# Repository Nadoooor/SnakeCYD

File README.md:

# SnakeCYD
--------------

--------------------------------

## Description:
SnakeCYD is a custom CYD, all in an PCB with snake slickscreen and with ESP32-s3 instead of a regular ESP32 chip.

## Why iam making this:
I was planning to get a CYD, but I got to know that it has a regular ESP32 on it instead of the S3, so i decided to make my own and add my snake slikscreen and also added bigger connectors for the wiring protocols and also some free pins.

## Featrues:

* Big JST connectors
* Free GPIO with PinSockets
* USB Type C
* Onboard Neopixel
* ESP32-S3 chip inside.

## Photos:

### PCB:

### 3D PCB:

### Schematic:
#### First Page:
--------------------

----------------------------
#### Second Page:

## Pinout:
| ESP32-S3 Pin Label | Signal / Net Name |
| :--- | :--- |
| **IO1** | `TFT_BL` |
| **IO4** | `TFT_DC` |
| **IO5** | `I2C_SDA` |
| **IO6** | `I2C_SCL` |
| **IO7** | `SPI_MOIS` |
| **IO8** | `SPI_CLK` |
| **IO9** | `SPI_MISO` |
| **IO10** | `ANY_CS` |
| **IO11** | `SPI2_MOIS` |
| **IO12** | `SPI2_CLK` |
| **IO13** | `SPI2_MISO` |
| **IO14** | `TFT_CS` |
| **IO15** | `T_CS` |
| **IO16** | `SD_CS` |
| **IO17** | `TX` |
| **IO18** | `RX` |
| **IO21** | `T_IRQ` |
| **TXD0** | `0TX` |
| **RXD0** | `0RX` |

## How to use:
1. Connect the SnakeCYD to you PC/Laptop.
2. Download the firmware source code you want to use.
3. Edit the pinout using the table above.
4. Build the firmware and flash it.
5. Enjoy.

## How to build:
1. Print the board.
2. Assemble all the components.
3. Enjoy.

# Made with ❤️, By Nadoooor

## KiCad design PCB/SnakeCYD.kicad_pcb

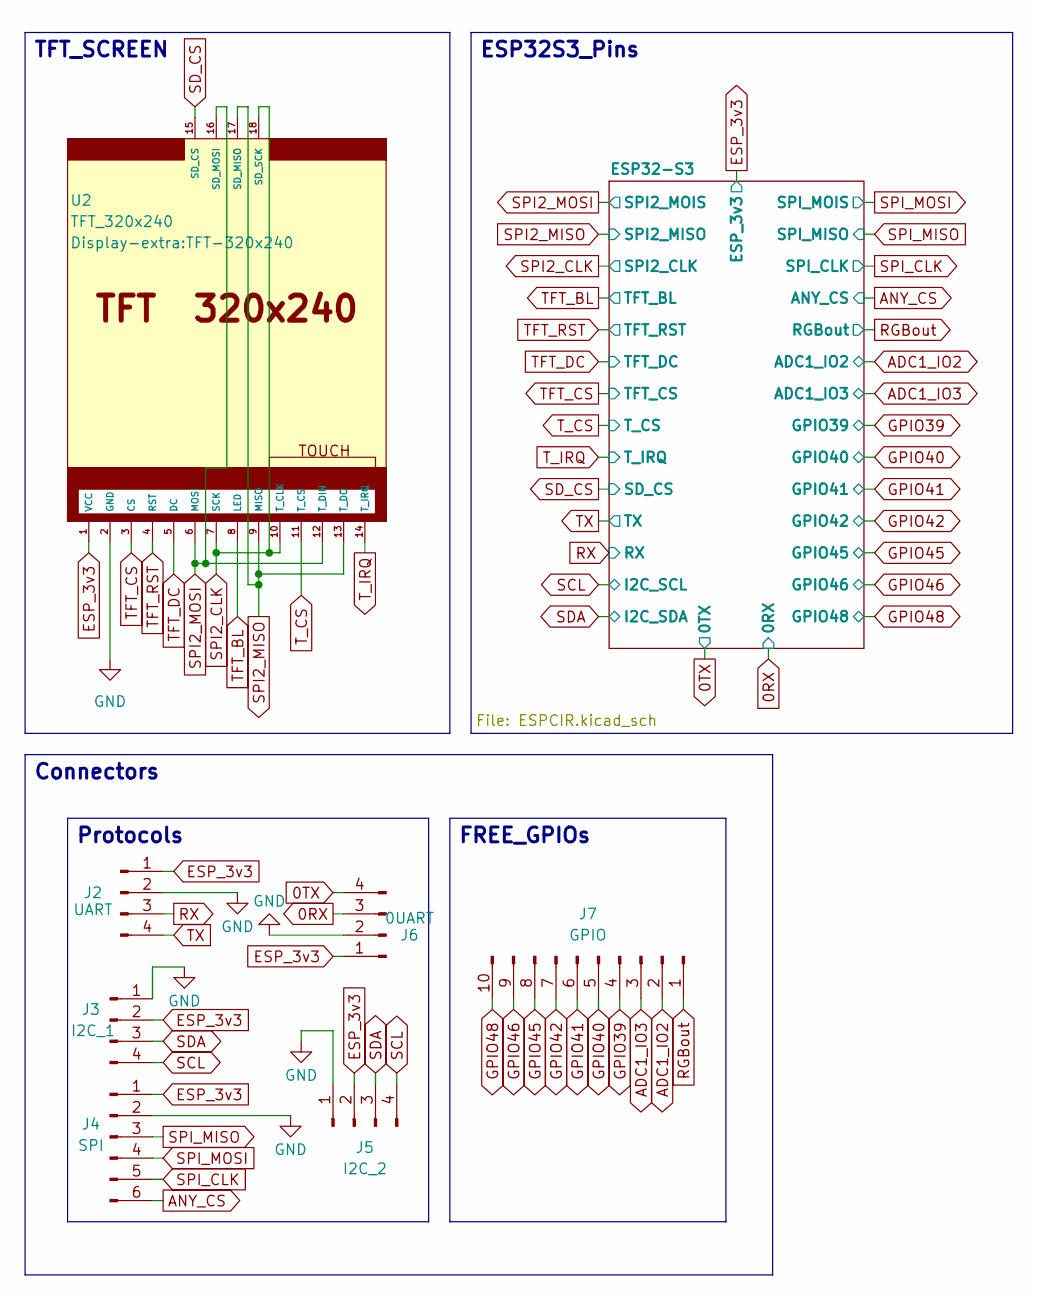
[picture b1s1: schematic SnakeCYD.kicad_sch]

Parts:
J2: UART; JST_XH_S4B-XH-A-1_1x04_P2.50mm_Horizontal
J3: I2C_1; JST_XH_S4B-XH-A-1_1x04_P2.50mm_Horizontal
J4: SPI; JST_XH_S6B-XH-A-1_1x06_P2.50mm_Horizontal
J5: I2C_2; JST_XH_S4B-XH-A-1_1x04_P2.50mm_Horizontal
J6: 0UART; JST_XH_S4B-XH-A-1_1x04_P2.50mm_Horizontal
J7: GPIO; PinSocket_1x10_P2.54mm_Horizontal
U2: TFT_320x240; TFT-320x240

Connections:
0RX: J6.3; also elsewhere on the board
0TX: J6.4; also elsewhere on the board
ADC1_IO2: J7.2; also elsewhere on the board
ADC1_IO3: J7.3; also elsewhere on the board
ANY_CS: J4.6; also elsewhere on the board
ESP_3v3: J2.1, J3.2, J4.1, J5.2, J6.1, U2.1 (VCC); also elsewhere on the board
GND: J2.2, J3.1, J4.2, J5.1, J6.2, U2.2 (GND); also elsewhere on the board
GPIO39: J7.4; also elsewhere on the board
GPIO40: J7.5; also elsewhere on the board
GPIO41: J7.6; also elsewhere on the board
GPIO42: J7.7; also elsewhere on the board
GPIO45: J7.8; also elsewhere on the board
GPIO46: J7.9; also elsewhere on the board
GPIO48: J7.10; also elsewhere on the board
RGBout: J7.1; also elsewhere on the board
RX: J2.3; also elsewhere on the board
SCL: J3.4, J5.4; also elsewhere on the board
SDA: J3.3, J5.3; also elsewhere on the board
SD_CS: U2.15 (SD_CS); also elsewhere on the board
SPI2_CLK: U2.7 (SCK), U2.10 (T_CLK), U2.18 (SD_SCK); also elsewhere on the board
SPI2_MISO: U2.9 (MISO), U2.13 (T_DO), U2.17 (SD_MISO); also elsewhere on the board
SPI2_MOSI: U2.6 (MOSI), U2.12 (T_DIN), U2.16 (SD_MOSI); also elsewhere on the board
SPI_CLK: J4.5; also elsewhere on the board
SPI_MISO: J4.3; also elsewhere on the board
SPI_MOSI: J4.4; also elsewhere on the board
TFT_BL: U2.8 (LED); also elsewhere on the board
TFT_CS: U2.3 (CS); also elsewhere on the board
TFT_DC: U2.5 (DC); also elsewhere on the board
TFT_RST: U2.4 (RST); also elsewhere on the board
TX: J2.4; also elsewhere on the board
T_CS: U2.11 (T_CS); also elsewhere on the board
T_IRQ: U2.14 (T_IRQ); also elsewhere on the board

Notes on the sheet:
TFT_SCREEN
Connectors
ESP32S3_Pins
Protocols
FREE_GPIOs

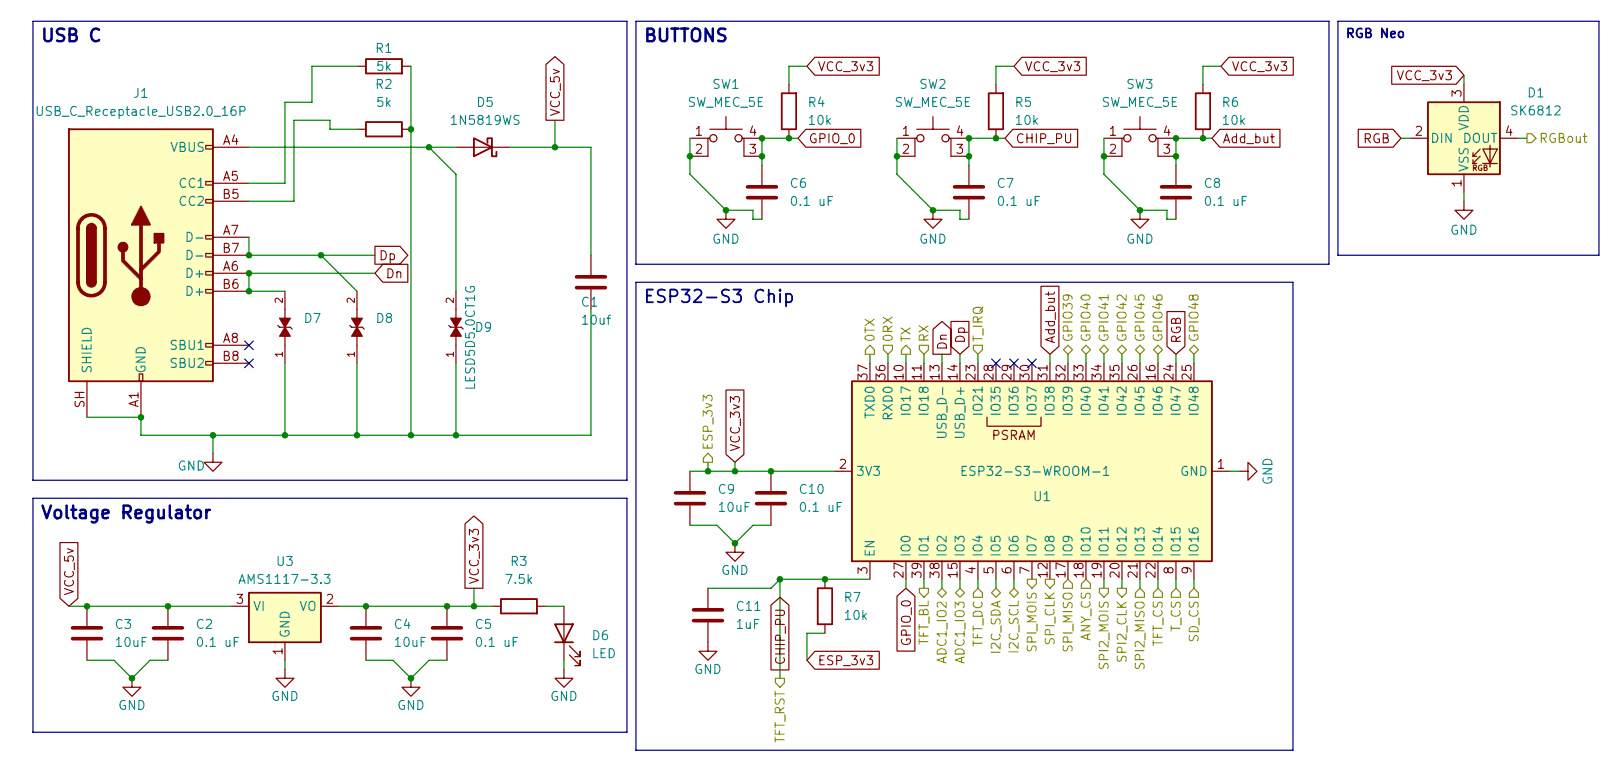
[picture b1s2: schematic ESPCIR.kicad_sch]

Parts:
C1: 10uf; C_0603_1608Metric_Pad1.08x0.95mm_HandSolder
C2, C5, C6, C7, C8, C10: 0.1 uF; C_0603_1608Metric_Pad1.08x0.95mm_HandSolder
C3, C4, C9: 10uF; C_0603_1608Metric_Pad1.08x0.95mm_HandSolder
C11: 1uF; C_0603_1608Metric_Pad1.08x0.95mm_HandSolder
D1: SK6812; LED_SK6812_PLCC4_5.0x5.0mm_P3.2mm
D5: 1N5819WS; D_SOD-323
D6: LED; LED_0603_1608Metric_Pad1.05x0.95mm_HandSolder
D7, D8, D9: LESD5D5.0CT1G; TVS_LESD5D5.0CT1G; PARTREV O
J1: USB_C_Receptacle_USB2.0_16P; USB_C_Receptacle_Amphenol_12401610E4-2A_CircularHoles
R1, R2: 5k; R_0603_1608Metric_Pad0.98x0.95mm_HandSolder
R3: 7.5k; R_0603_1608Metric_Pad0.98x0.95mm_HandSolder
R4, R5, R6, R7: 10k; R_0603_1608Metric_Pad0.98x0.95mm_HandSolder
SW1, SW2, SW3: SW_MEC_5E; SW_Push_1P1T_NO_CK_KMR2
U1: ESP32-S3-WROOM-1
U3: AMS1117-3.3; SOT-223-3_TabPin2

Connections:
0RX: U1.36 (RXD0); also elsewhere on the board
0TX: U1.37 (TXD0); also elsewhere on the board
ADC1_IO2: U1.38 (IO2); also elsewhere on the board
ADC1_IO3: U1.15 (IO3); also elsewhere on the board
ANY_CS: U1.18 (IO10); also elsewhere on the board
Add_but: C8.1, R6.1, SW3.3 (K), SW3.4 (A), U1.31 (IO38); also elsewhere on the board
Dn: D7.2, J1.A6 (D+), J1.B6 (D+), U1.13 (USB_D-)
Dp: D8.2, J1.A7 (D-), J1.B7 (D-), U1.14 (USB_D+)
ESP_3v3: C4.1, C5.1, C9.1, C10.1, D1.3 (VDD), R3.1, R4.2, R5.2, R6.2, R7.2, U1.2 (3V3), U3.2 (VO); also elsewhere on the board
GND: C1.2, C2.2, C3.2, C4.2, C5.2, C6.2, C7.2, C8.2, C9.2, C10.2, C11.2, D1.1 (VSS), D6.1 (K), D7.1, D8.1, D9.1, J1.A1 (GND), J1.A12 (GND), J1.B1 (GND), J1.B12 (GND), J1.SH (SHIELD), R1.2, R2.2, SW1.1, SW1.2, SW2.1, SW2.2, SW3.1, SW3.2, U1.1 (GND), U1.40 (GND), U1.41 (GND), U3.1 (GND); also elsewhere on the board
GPIO39: U1.32 (IO39); also elsewhere on the board
GPIO40: U1.33 (IO40); also elsewhere on the board
GPIO41: U1.34 (IO41); also elsewhere on the board
GPIO42: U1.35 (IO42); also elsewhere on the board
GPIO45: U1.26 (IO45); also elsewhere on the board
GPIO46: U1.16 (IO46); also elsewhere on the board
GPIO48: U1.25 (IO48); also elsewhere on the board
GPIO_0: C6.1, R4.1, SW1.3 (K), SW1.4 (A), U1.27 (IO0); also elsewhere on the board
unnamed: D5.2 (A), D9.2, J1.A4 (VBUS), J1.A9 (VBUS), J1.B4 (VBUS), J1.B9 (VBUS)
unnamed: D6.2 (A), R3.2
unnamed: J1.A5 (CC1), R1.1
unnamed: J1.B5 (CC2), R2.1
RGB: D1.2 (DIN), U1.24 (IO47)
RGBout: D1.4 (DOUT); also elsewhere on the board
RX: U1.11 (IO18); also elsewhere on the board
SCL: U1.6 (IO6); also elsewhere on the board
SDA: U1.5 (IO5); also elsewhere on the board
SD_CS: U1.9 (IO16); also elsewhere on the board
SPI2_CLK: U1.20 (IO12); also elsewhere on the board
SPI2_MISO: U1.21 (IO13); also elsewhere on the board
SPI2_MOSI: U1.19 (IO11); also elsewhere on the board
SPI_CLK: U1.12 (IO8); also elsewhere on the board
SPI_MISO: U1.17 (IO9); also elsewhere on the board
SPI_MOSI: U1.7 (IO7); also elsewhere on the board
TFT_BL: U1.39 (IO1); also elsewhere on the board
TFT_CS: U1.22 (IO14); also elsewhere on the board
TFT_DC: U1.4 (IO4); also elsewhere on the board
TFT_RST: C7.1, C11.1, R5.1, R7.1, SW2.3 (K), SW2.4 (A), U1.3 (EN); also elsewhere on the board
TX: U1.10 (IO17); also elsewhere on the board
T_CS: U1.8 (IO15); also elsewhere on the board
T_IRQ: U1.23 (IO21); also elsewhere on the board
VCC_5v: C1.1, C2.1, C3.1, D5.1 (K), U3.3 (VI)

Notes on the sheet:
USB C
ESP32-S3 Chip
RGB Neo
BUTTONS
Voltage Regulator

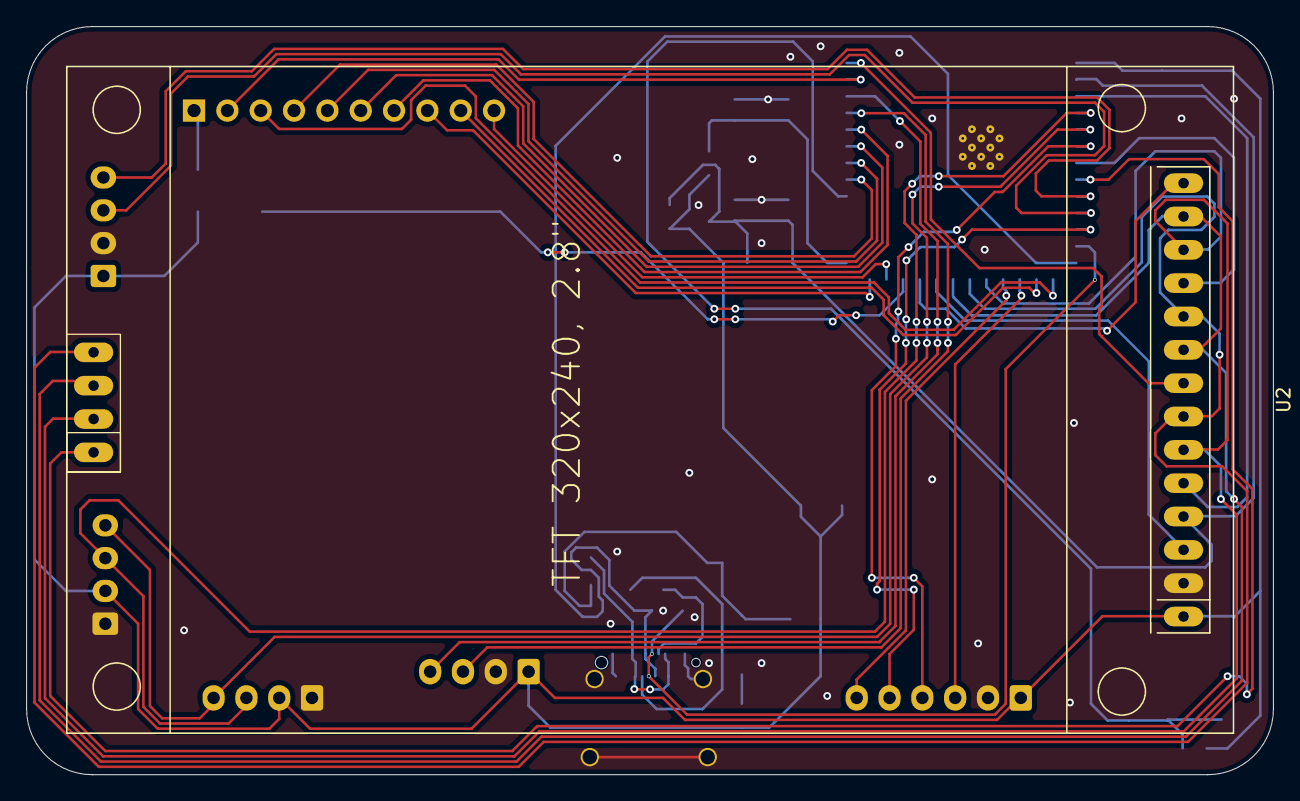
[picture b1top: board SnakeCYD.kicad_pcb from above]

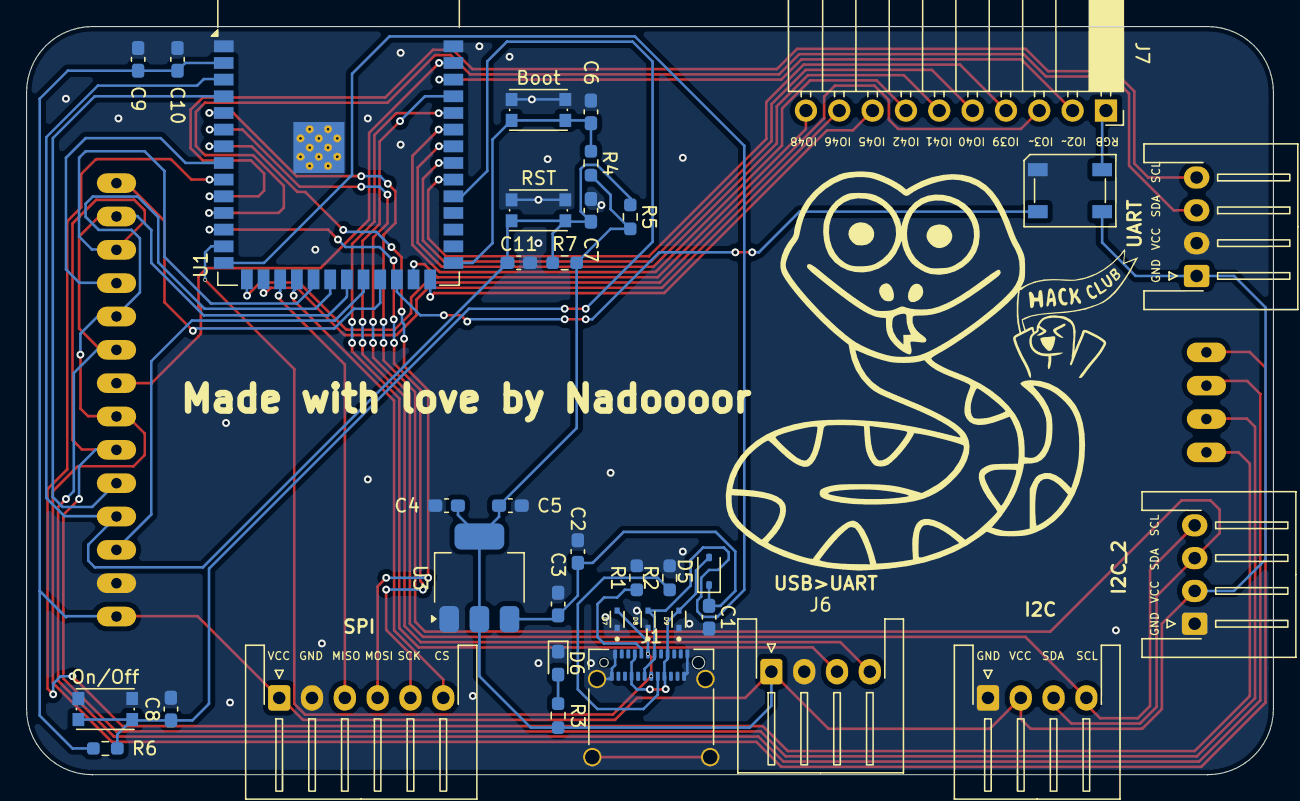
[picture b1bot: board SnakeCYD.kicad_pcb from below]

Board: 2 copper layers, 95.0 x 57.0 mm, 37 parts (36 on the bottom side), 42 nets.

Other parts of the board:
Boot: SW_MEC_5E; SW_Push_1P1T_NO_CK_KMR2
On/Off: SW_MEC_5E; SW_Push_1P1T_NO_CK_KMR2
RST: SW_MEC_5E; SW_Push_1P1T_NO_CK_KMR2

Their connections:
Add_but: On/Off.3 (K), On/Off.4 (A); also elsewhere on the board
GND: Boot.1, Boot.2, On/Off.1, On/Off.2, RST.1, RST.2; also elsewhere on the board
GPIO_0: Boot.3 (K), Boot.4 (A); also elsewhere on the board
TFT_RST: RST.3 (K), RST.4 (A); also elsewhere on the board
